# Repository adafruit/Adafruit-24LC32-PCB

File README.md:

## Adafruit 24LC32 I2C EEPROM Breakout PCB

<a href="http://www.adafruit.com/products/5146"><br/>
Click here to purchase one from the Adafruit shop</a>

PCB files for the Adafruit 24LC32 I2C EEPROM Breakout. 

Format is EagleCAD schematic and board layout
* https://www.adafruit.com/product/5146

### Description

If you want to store calibration values, MAC addresses, non-secure access tokens, or other unique identifiers, EEPROM storage is a great option. EEPROM is long lasting, and doesn't need to be written in pages - a single byte can be written at once (unlike with flash memory!) EEPROM storage persists even when the power goes out, and can be over-written literally one million times.

Some microcontrollers, like the ATmega328, have built in EEPROM, usually around 64 to 1024 bytes of it. But some, especially ARM Cortex's, don't! What then? that's where this petite Adafruit 24LC32 I2C EEPROM Breakout comes in to help! With 32 Kbit (4 KByte) of storage, and handy chainable Stemma QT connectors, it's just the right amount of simple I2C-controllable storage. Since its external to your microcontroller or microcomputer, uploading new flash memory won't wipe the data from this chip.

We use the CAT24C32 (or equivalent) EEPROM, internally organized as 4096 words of 8 bits each. It features a 32 byte page write buffer (if you want to write faster than one byte at a time). Use 2 to 5V power/logic and up to 1 MHz clocked I2C. The default I2C address is 0x50 and there are three external address pins / jumpers to allow addressing of up to eight EEPROM devices on the same bus.

To make things easier and a bit more flexible, we've also included SparkFun Qwiic compatible STEMMA QT connectors for the I2C bus so you don't even need to solder! Just plug in a compatible cable and attach it to your MCU of choice, and you’re ready to store and retrieve from a reliable and durable EEPROM. QT Cable is not included, but we have a variety in the shop. 

### License

Adafruit invests time and resources providing this open source design, please support Adafruit and open-source hardware by purchasing products from [Adafruit](https://www.adafruit.com)!

Designed by Limor Fried/Ladyada for Adafruit Industries.

Creative Commons Attribution/Share-Alike, all text above must be included in any redistribution. 
See license.txt for additional details.

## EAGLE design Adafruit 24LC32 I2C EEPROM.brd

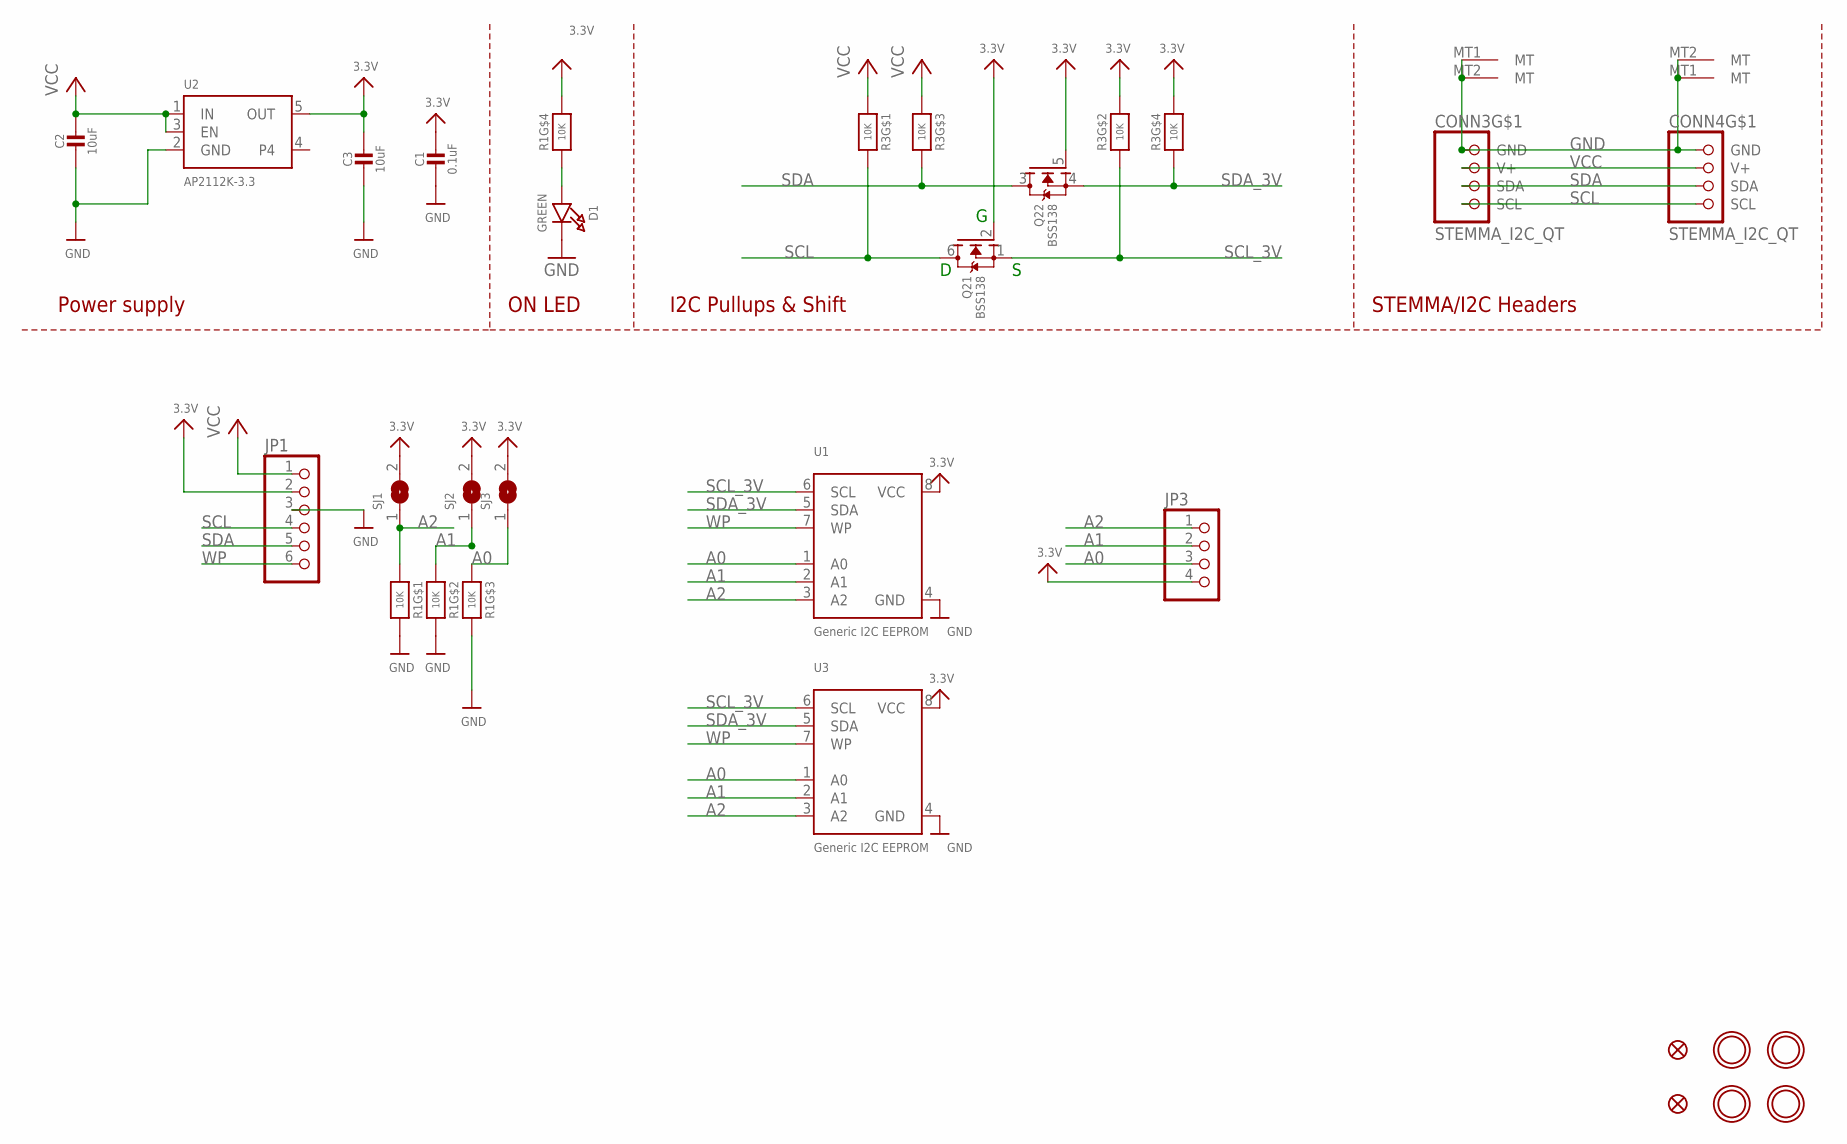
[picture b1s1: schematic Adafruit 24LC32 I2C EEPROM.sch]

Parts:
C1: 0.1uF; 0603-NO
C2, C3: 10uF; 0805-NO
CONN3, CONN4: STEMMA_I2C_QT; JST_SH4
D1: GREEN; CHIPLED_0603_NOOUTLINE
FID3, FID4: FIDUCIAL_1MM
JP1: HEADER-1X670MIL; 1X06_ROUND_70
JP3: HEADER-1X4ROUND; 1X04_ROUND
Q2: BSS138; SOT363
R1, R3: 10K; RESPACK_4X0603
SJ1, SJ2, SJ3: SOLDERJUMPER; SOLDERJUMPER_ARROW_NOPASTE
U1: Generic I2C EEPROM; SOIC8_150MIL
U2: AP2112K-3.3; SOT23-5
U3: Generic I2C EEPROM; USON8
U$1, U$17, U$19, U$21: MOUNTINGHOLE2.5; MOUNTINGHOLE_2.5_PLATED

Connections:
3.3V: C1.1, C3.1, JP1.2, JP3.4, Q2.2 (G), Q2.5 (G), R1.5 (2), R3.2 (1), R3.4 (1), SJ1.2, SJ2.2, SJ3.2, U1.8 (VCC), U2.5 (OUT), U3.8 (VCC)
A0: JP3.3, R1.3 (1), SJ3.1, U1.1 (A0), U3.1 (A0)
A1: JP3.2, R1.2 (1), SJ2.1, U1.2 (A1), U3.2 (A1)
A2: JP3.1, R1.1, SJ1.1, U1.3 (A2), U3.3 (A2)
GND: C1.2, C2.2, C3.2, CONN3.1 (GND), CONN3.MT1 (MT), CONN3.MT2 (MT), CONN4.1 (GND), CONN4.MT1 (MT), CONN4.MT2 (MT), D1.C, JP1.3, R1.6 (2), R1.7 (2), R1.8 (2), U1.4 (GND), U2.2 (GND), U3.4 (GND)
unnamed: D1.A, R1.4 (1)
SCL: CONN3.4 (SCL), CONN4.4 (SCL), JP1.4, Q2.6 (D), R3.8 (2)
SCL_3V: Q2.1 (S), R3.7 (2), U1.6 (SCL), U3.6 (SCL)
SDA: CONN3.3 (SDA), CONN4.3 (SDA), JP1.5, Q2.3 (D), R3.6 (2)
SDA_3V: Q2.4 (S), R3.5 (2), U1.5 (SDA), U3.5 (SDA)
VCC: C2.1, CONN3.2 (V+), CONN4.2 (V+), JP1.1, R3.1, R3.3 (1), U2.1 (IN), U2.3 (EN)
WP: JP1.6, U1.7 (WP), U3.7 (WP)

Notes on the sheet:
I2C Pullups & Shift
STEMMA/I2C Headers
ON LED
Power supply

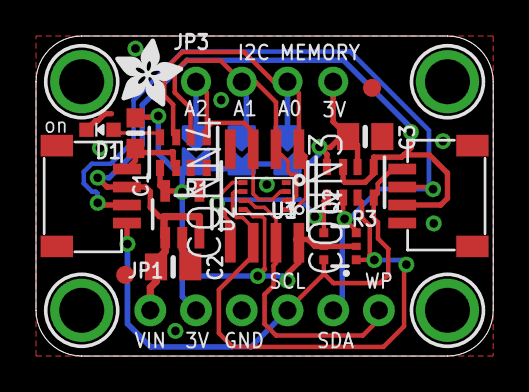
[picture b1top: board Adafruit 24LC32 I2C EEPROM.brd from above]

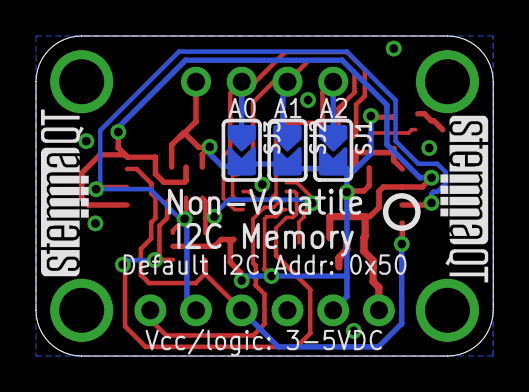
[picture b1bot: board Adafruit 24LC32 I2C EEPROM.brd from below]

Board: 2 copper layers, 25.4 x 17.8 mm, 27 parts (6 on the bottom side), 12 nets.

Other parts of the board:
U$25: PCBFEAT-REV-040
U$30, U$31: STEMMAQT
U$32: ADAFRUIT_3.5MM

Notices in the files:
parts and their libraries:
microbuilder: This work is placed in the public domain, and may be freely used for commercial and non-commercial work with the following conditions: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
